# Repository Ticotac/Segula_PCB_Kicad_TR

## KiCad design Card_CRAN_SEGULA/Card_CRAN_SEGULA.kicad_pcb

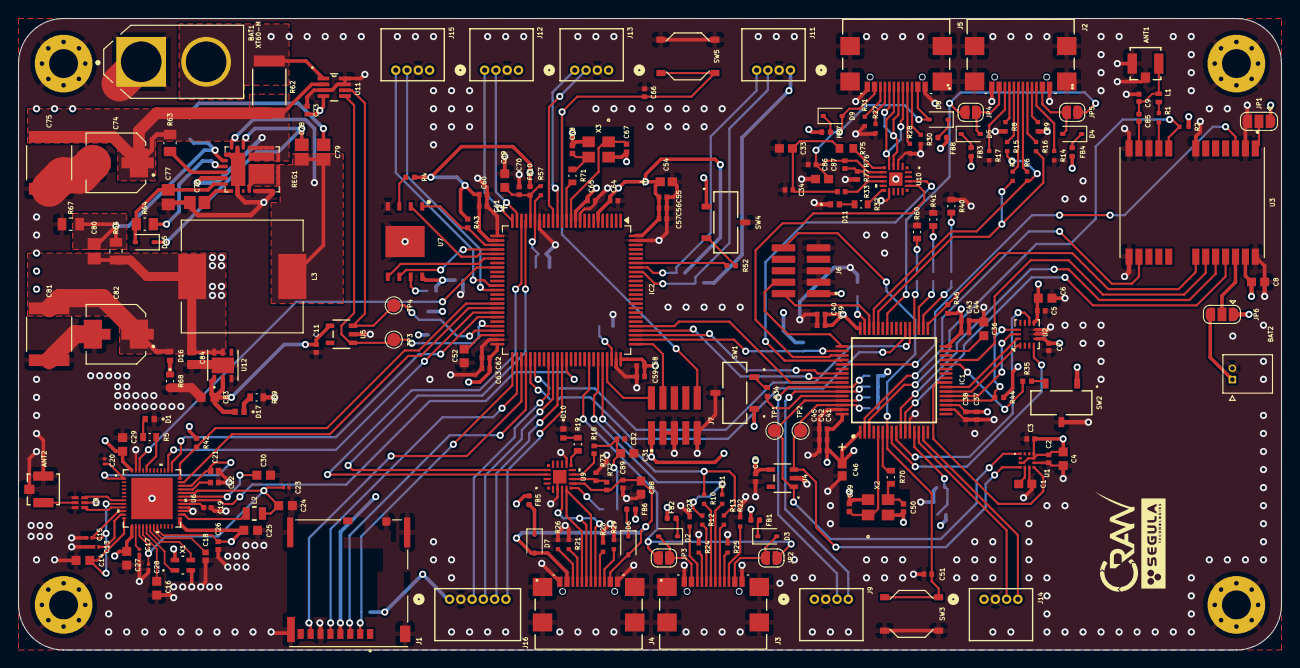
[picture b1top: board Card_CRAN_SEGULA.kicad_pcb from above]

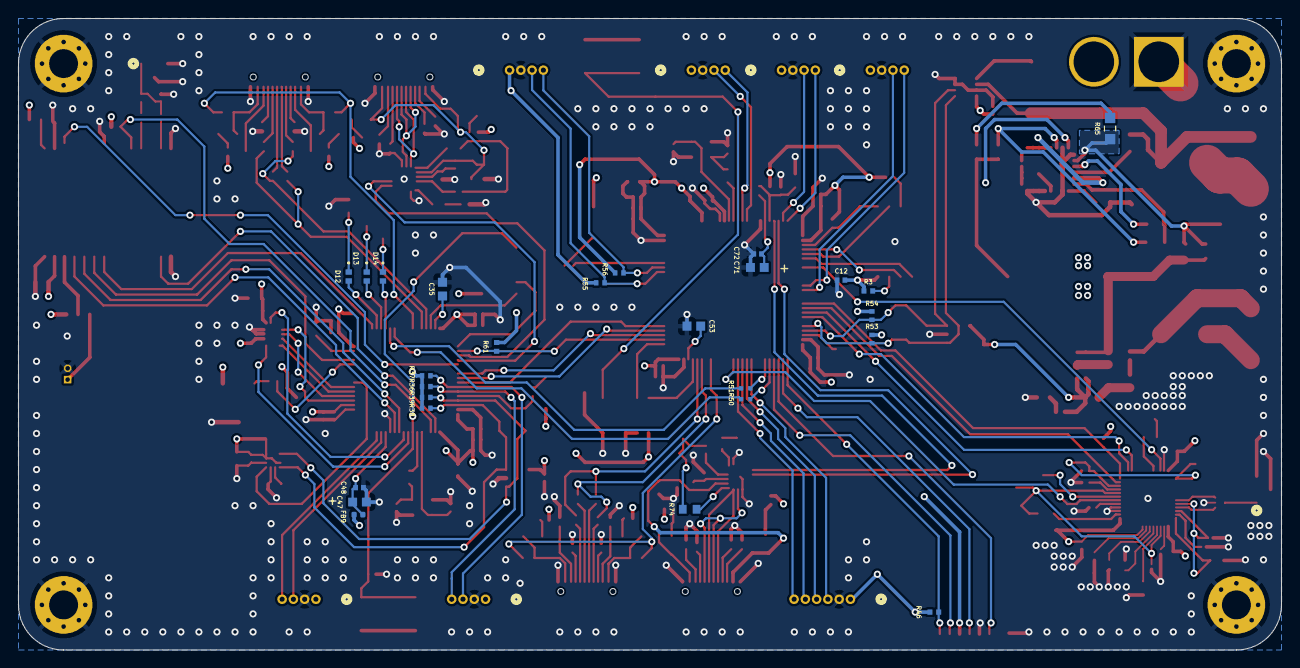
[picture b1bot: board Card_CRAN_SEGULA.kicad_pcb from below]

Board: 4 copper layers, 140.0 x 70.0 mm, 246 parts (26 on the bottom side), 193 nets.

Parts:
ANT1, ANT2: RECE.20279.001E.01; CON3_RECE.20279.001E.01_TAL
BAT1: XT60-M; AMASS_XT60-M
BAT2: 530480210; MOLEX_530480210
C1: 220nF; CAPC17595_87N_KEM
C2, C3, C10, C11, C12, C32, C34, C37, C38, C39, C40, C41, C42, C43, C44, C45, C48, C51, C55, C56, C57, C58, C59, C60, C61, C62, C63, C64, C65, C66, C70, C72, C73, C86, C89: 100nF; CAPC1005X55N
C4, C83, C84: 10uF; CAPC1608X100N
C5: 0.1uF; CAPC1005X55N
C6, C16, C29, C30, C35, C36, C52, C53: 2.2uF; CAPC1608X100N
C7, C9, C19: 10nF; CAPC1005X55N
C8, C31, C33, C87, C88: 1uF; CAPC17595_90N_KEM
C13, C23: 0.47uF; CAPC0603X33N
C14, C24, C25, C27: 4.7uF; CAPC1608X100N
C15, C20: 100nF; CAPC0603X33N
C17: 22nF; CAPC0603X33N
C18: 1uF; CAPC1005X70N
C21: 2.2uF; CAPC1005X70N
C22, C26: 1uF; CAPC1005X60N
C28: 0.22uF; CAPC0603X33N
C46, C54: 10uF; CAPMP2.1X1.25_1N_KEM
C47, C69, C71: 1uF; TACL_AVX
C49, C50, C67, C68: 10pF; CAP_0402C_AVX
C74, C82: 100uF; CAP_EEEFPV101XAV
C75, C81: 47uF; CAP_C5750X7R1V476M230KC
C76, C77: 2.2uF; CAPC220145_140N_KEM
C78, C79: 100nF; CAPC230155_120N_KEM
C80: 4.7nF; CAPC220145_100N_KEM
C85: 22pF; CAPC1005X55N
D1, D13: Blue; 599-0091-007F_DIA
D2, D3, D4, D5, D6, D7, D8, D9, D15: SD103AWS; D_SOD-323
D10, D11: RED; 599-0001-007F_DIA
D12, D14: Yellow; 599-0004-007F_DIA
D16: LED; 599-0081-007F_DIA
D17: Green; 599-0081-007F_DIA
FB1, FB2, FB3, FB4, FB5, FB6, FB7, FB8, FB9, FB10: FerriteBead_Small; L_0402_1005Metric
H1, H2, H3, H4: MountingHole_Pad; MountingHole_3.2mm_M3_Pad_Via
IC1: STM32F405RGT6; QFP50P1200X1200X160-64N
IC2: STM32H753VIT6; LQFP-100_14x14mm_P0.5mm
J1: 503398-1892; MOLEX_503398-1892
J2, J3, J4, J5: USB4110GFA; USB4110-GF-A_GCT
J6, J7: M50-3600542R; HARWIN_M50-3600542R
J9, J11, J12, J13, J14, J15: 530480410; CONN04_530480410_MOL
J16: 530480610; CONN06_530480610_MOL
JP1, JP6: SolderJumper_3_Open; SolderJumper-3_P1.3mm_Open_RoundedPad1.0x1.5mm
JP2, JP3, JP4, JP5: SolderJumper_2_Open; SolderJumper-2_P1.3mm_Open_RoundedPad1.0x1.5mm
L1: 27nH; INDC1006X60N
L2: 3.3uH; WE-PMI_0805_H1
L3: 15uH; IND_SRP1265A-150M
R1, R2, R50, R51: 10R; RES_ERA2AKD100X
R3, R4, R34, R35, R42, R43, R44, R45, R46, R52, R61: 10kR; RESC1105X40N
R5, R41: 100R; RES_ERJPA3D1000V
R6, R7, R10, R11, R12, R13, R15, R16: 22R; RES_ERA2AKD220X
R8, R14, R20, R23, R25, R26, R27, R30: 100kR; RES_ERJ2RKF1003X
R9, R17, R21, R22, R24, R28, R29, R31: 5.1kR; RES_ERJ2RKF5101X
R18, R33: 1kR; RESC1005X40N
R19, R32, R40, R60: 330R; RES_ERJPA3D3300V
R36, R37, R38, R39, R53, R54, R55, R56: 4.7kR; RESC1005X40N
R57: 47R; RES_ERA2AED470X
R62: 0.01R; RES_PE2512_YAG
R63, R64: 10kR; RESC2012X70N
R65: 19.6kR; RES_ERJ-PB6B1962V
R66: 6.8kR; RESC2012X60N
R67: 1.3kR; RK73H2ATTD1301F
R68: 560R; RES_ERJPA3F5600V
R69: 240R; RES_ERJPA3F2400V
R70, R71: 620R; RES_ERJPA3F6200V
R72, R76: 22.1kR; RESC1005X40N
R73, R77: 47.5kR; RESC1005X40N
R74, R75: 0R; RESC1508X50N
REG1: MIC26903YJL-TR; MIC24054YJLTR
SW1, SW2, SW4: TDD01H0SB1R; SOT_TDDSB1R_CNK
SW3, SW5: SMD-BUTTON_4P-5.2X5.2X1.5MM-SKQGADE010_; SW4-SMD-5.2X5.2X1.5MM
TP1, TP2, TP3, TP4: TestPoint; TestPoint_Pad_D1.5mm
U1: IIS2MDCTR
U2: IIM-42652; Bosch_LGA-14_3x2.5mm_P0.5mm
U3: NEO-M9N-00B; XCVR_NEO-M9N-00B
U4, U5: 24CW1280T-I/OT; SOT-23-5_2P9X1P6_MCH
U6: NRF7002-QFAA-R; QFN48_6X6_NOR
U7: W25N01GVZEIG_TR; SON127P800X600X80-9N-D
U8: DPX165950DT-8148A1; RF_5049A1_TDK
U9, U10: CP2102N-A02-GQFN20R; QFN20_SIL
U11: INA219AIDCNR; DCN8
U12: LD39200PU33R; SON_DFN6_3X3_STM
X1: NX2016SA-40M-STD-CZS-3; NX2016SA-40M-STD-CZS-3_NDK
X2, X3: ABM8G-25.000MHZ-4Y-T3; ABM8G_ABR

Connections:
+5V: C80.1, C81.1, C82.1, C84.1, D16.2 (A), FB1.1, FB2.2, FB3.1, FB4.2, FB5.1, FB6.2, FB7.1, FB8.2, L3.2, R66.1, U12.5 (EN), U12.6 (IN)
ADC123_0_COM: IC2.16 (PC1), J13.3
ADC123_1_COM: IC2.15 (PC0), J13.4
BOOT0_COM: IC2.94 (BOOT0), R52.1
BOOT0_NAV: IC1.60 (BOOT0), R34.1
BOOT1_NAV: IC1.28 (PB2), R35.1
FLASH_CS: IC2.28 (PA4), R43.2, U7.1 (~CS)
FLASH_MISO: IC2.30 (PA6), U7.2 (DO_(IO1))
FLASH_MOSI: IC2.31 (PA7), U7.5 (DI_(IO0))
FLASH_SCK: IC2.29 (PA5), U7.6 (CLK)
GND: ANT1.2 (GND), ANT1.3 (GND), ANT2.2 (GND), ANT2.3 (GND), BAT1.1 (-), BAT2.2, C1.2, C2.2, C3.2, C4.2, C5.2, C6.2, C7.2, C8.1, C9.1, C10.2, C11.2, C12.1, C13.1, C14.2, C15.1, C16.1, C17.2, C18.1, C19.1, C20.1, C21.1, C22.1, C23.2, C24.2, C25.2, C26.1, C27.1, C28.1, C29.2, C30.1, C31.2, C32.2, C33.2, C34.2, C35.2, C36.2, C37.2, C38.2, C39.2, C40.2, C41.2, C42.2, C43.2, C44.2, C45.2, C46.2, C47.2, C48.2, C49.2, C50.1, C51.2, C52.2, C53.2, C54.2, C55.2, C56.2, C57.2, C58.2, C59.2, C60.2, C61.2, C62.2, C63.2, C64.2, C65.2, C66.2, C67.2, C68.1, C69.2, C70.1, C71.2, C72.1, C73.1, C74.2, C75.2, C76.2, C77.2, C81.2, C82.2, C83.2, C84.2, C86.2, C87.2, C88.2, C89.2, D1.1 (K), D10.1 (K), D11.1 (K), H1.1, H2.1, H3.1, H4.1, IC1.12 (VSSA), IC1.18 (VSS_1), IC1.63 (VSS_2), IC2.10 (VSS), IC2.19 (VSSA), IC2.26 (VSS), IC2.49 (VSS), IC2.74 (VSS), IC2.99 (VSS), J1.6 (VSS), J1.9 (VSS__1), J1.P1 (SHIELD), J1.P2 (SHIELD__1), J1.P3 (SHIELD__2), J1.P4 (SHIELD__3), J2.15 (S1), J2.16 (S2), J2.17 (S3), J2.18 (S4), J2.A1/B12 (GND), J2.A12/B1 (GND), J3.15 (S1), J3.16 (S2), J3.17 (S3), J3.18 (S4), J3.A1/B12 (GND), J3.A12/B1 (GND), J4.15 (S1), J4.16 (S2), J4.17 (S3), J4.18 (S4), J4.A1/B12 (GND), J4.A12/B1 (GND), J5.15 (S1), J5.16 (S2), J5.17 (S3), J5.18 (S4), J5.A1/B12 (GND), J5.A12/B1 (GND), J6.3, J6.5, J6.9, J7.3, J7.5, J7.9, J9.2, J11.2, J12.2, J13.2, J14.2, J15.2, J16.2, JP1.3 (B), R8.1, R9.1, R14.2, R17.1, R20.1, R21.1, R22.1, R23.2, R24.1, R25.1, R26.2, R27.1, R28.1, R29.1, R30.2, R31.1, R40.2, R41.1, R60.2, R67.2, R68.2, R69.2, R73.2, R77.2, REG1.2 (PGND), REG1.5 (PGND), REG1.6 (PGND), REG1.7 (PGND), REG1.8 (PGND), REG1.21 (PGND), REG1.23 (SGND), REG1.31 (PGND), SW1.2, SW2.2, SW3.3 (B0), SW3.4 (B1), SW4.2, SW5.3 (B0), SW5.4 (B1), U1.6 (GND_1), U1.8 (GND_2), U2.6 (GND), U2.7 (GND), U3.2 (D_SEL), U3.7 (V_USB), U3.10 (GND), U3.12 (GND__1), U3.13 (GND__2), U3.24 (GND__3), U4.2 (VSS), U5.2 (VSS), U6.27 (BUCKVSS), U6.28 (BUCKVSS), U6.47 (VSS), U6.49 (VSS), U7.4 (GND), U7.9 (EP), U8.2, U8.4, U8.6, U9.3 (GND), U9.12 (GND__1), U9.21 (GND__2), U10.3 (GND), U10.12 (GND__1), U10.21 (GND__2), U11.3 (GND), U11.7 (A0), U11.8 (A1), U12.3 (GND), U12.7 (GND), X1.2, X1.4, X2.2, X2.4, X3.2, X3.4
GNSS_BAT_BACKUP: JP6.2 (C), U3.22 (V_BCKP)
GNSS_CLK: IC1.29 (PB10), U3.19 (SCL/SPI_CLK)
GNSS_CS: IC1.33 (PB12), R45.1, U3.18 (SDA/SPI_CS_N)
GNSS_LNA_EN: IC1.2 (PC13), U3.14 (LNA_EN)
GNSS_NRST: IC1.3 (PC14), R2.2, U3.8 (RESET_N)
GNSS_PPS: IC1.53 (PC12), U3.3 (TIMEPULSE)
GNSS_SDI: IC1.11 (PC3), U3.21 (RXD/SPI_MOSI)
GNSS_SDO: IC1.10 (PC2), U3.20 (TXD/SPI_MISO)
HSE_IN_COM: C67.1, IC2.12 (PH0), X3.1
HSE_IN_NAV: C49.1, IC1.5 (PH0), X2.1
HSE_OUT_COM: IC2.13 (PH1), R71.2
HSE_OUT_NAV: IC1.6 (PH1), R70.2
I2C2_SDA_COM: IC2.93 (PB7), J11.4, R56.2
I2C2_SDA_NAV: IC1.59 (PB7), J9.4, R36.2
I2C2_SLC_COM: IC2.92 (PB6), J11.3, R55.2
I2C2_SLC_NAV: IC1.58 (PB6), J9.3, R37.2
I2C_SCL_COM: IC2.46 (PB10), R53.2, TP3.1, U5.1 (SCL), U11.5 (SCL)
I2C_SCL_NAV: IC1.61 (PB8), R39.2, TP1.1, U1.1 (SCL/SPC), U4.1 (SCL)
I2C_SDA_COM: IC2.47 (PB11), R54.2, TP4.1, U5.3 (SDA), U11.6 (SDA)
I2C_SDA_NAV: IC1.62 (PB9), R38.2, TP2.1, U1.4 (SDA/SDI/SDO), U4.3 (SDA)
IMU_ACC_INT: IC1.8 (PC0), U2.4 (INT1/INT)
IMU_CS: IC1.20 (PA4), R44.2, U2.12 (AP_CS)
IMU_GYR_INT: IC1.9 (PC1), U2.9 (INT2/FSYNC/CLKIN)
IMU_SCLK: IC1.21 (PA5), U2.13 (AP_SCL/AP_SCLK)
IMU_SD0: IC1.22 (PA6), U2.1 (AP_SDO/AP_AD0)
IMU_SDI: IC1.23 (PA7), U2.14 (AP_SDA/AP_SDIO/AP_SDI)
LED_A_NAV: D12.2 (A), IC1.34 (PB13)
LED_B_NAV: D13.2 (A), IC1.35 (PB14)
LED_C_NAV: D14.2 (A), IC1.36 (PB15)
MAG_INT: IC1.24 (PC4), U1.7 (INT/DRDY)
NRST_COM: C66.1, IC2.14 (NRST), J7.10, SW5.1 (A0), SW5.2 (A1)
NRST_NAV: C51.1, IC1.7 (NRST), J6.10, SW3.1 (A0), SW3.2 (A1)
unnamed: ANT1.1 (SIGNAL), C9.2, C85.1, L1.1
unnamed: ANT2.1 (SIGNAL), U8.5
unnamed: C31.1, C32.1, R18.2, R74.2
unnamed: C33.1, C34.1, R33.2, R75.2
unnamed: C50.2, R70.1, X2.3
unnamed: C52.1, IC2.48 (VCAP)
unnamed: C53.1, IC2.73 (VCAP)
unnamed: C68.2, R71.1, X3.3
unnamed: C79.2, R65.1
unnamed: D1.2 (A), R5.2
unnamed: D2.2 (A), J3.A4/B9 (VBUS), JP3.1 (A)
unnamed: D2.1 (K), FB2.1
unnamed: D3.2 (A), J3.A9/B4 (VBUS), JP2.1 (A)
unnamed: D3.1 (K), FB1.2
unnamed: D4.2 (A), J2.A4/B9 (VBUS), JP5.1 (A)
unnamed: D4.1 (K), FB4.1
unnamed: D5.2 (A), J2.A9/B4 (VBUS), JP4.1 (A)
unnamed: D5.1 (K), FB3.2
unnamed: D6.1 (K), FB6.1
unnamed: D7.1 (K), FB5.2
unnamed: D8.1 (K), FB8.1
unnamed: D9.1 (K), FB7.2
unnamed: D10.2 (A), R19.1
unnamed: D11.2 (A), R32.1
unnamed: D12.1 (K), R40.1
unnamed: D13.1 (K), R41.2
unnamed: D14.1 (K), R60.1
unnamed: C77.1, D15.2 (A), R64.1, REG1.28 (VDD)
unnamed: D16.1 (K), R68.1
unnamed: D17.1 (K), R69.1
unnamed: C36.1, IC1.31 (VCAP_1)
unnamed: C35.1, IC1.47 (VCAP_2)
unnamed: J2.A5 (CC1), R9.2
unnamed: J2.B5 (CC2), R17.2
unnamed: J2.A7 (DN1), R7.2
unnamed: J2.B7 (DN2), R16.2
unnamed: J2.A6 (DP1), R6.2
unnamed: J2.B6 (DP2), R15.1
unnamed: J2.A8 (SBU1), R8.2
unnamed: J2.B8 (SBU2), R14.1
unnamed: J3.A5 (CC1), R24.2
unnamed: J3.B5 (CC2), R22.2
unnamed: J3.A7 (DN1), R11.2
unnamed: J3.B7 (DN2), R12.2
unnamed: J3.A6 (DP1), R10.2
unnamed: J3.B6 (DP2), R13.1
unnamed: J3.A8 (SBU1), R25.2
unnamed: J3.B8 (SBU2), R23.1
unnamed: J4.A5 (CC1), R21.2
unnamed: J4.B5 (CC2), R29.2
unnamed: J4.A8 (SBU1), R20.2
unnamed: J4.B8 (SBU2), R26.1
unnamed: J5.A5 (CC1), R28.2
unnamed: J5.B5 (CC2), R31.2
unnamed: J5.A8 (SBU1), R27.2
unnamed: J5.B8 (SBU2), R30.1
unnamed: JP1.2 (C), U3.1 (SAFEBOOT_N)
unnamed: BAT2.1, JP6.3 (B)
unnamed: L1.2, R1.1
unnamed: R34.2, SW1.3
unnamed: R35.2, SW2.3
unnamed: R52.2, SW4.3
unnamed: C76.1, REG1.1 (PVDD)
unnamed: C1.1, U1.5 (C1)
unnamed: C85.2, U3.11 (RF_IN)
unnamed: R1.2, U3.9 (VCC_RF)
unnamed: L2.1, U6.26 (BUCKOUT)
unnamed: C14.1, C15.2, U6.8 (PAVDD<1>), U6.10 (PAVDD<0>), U6.12 (PALDO)
unnamed: R5.1, U6.44 (SW_CTRL0)
unnamed: R3.2, U7.7 (~HOLD_(IO3))
unnamed: R4.2, U7.3 (~WP_(IO2))
unnamed: R72.2, R73.1, U9.8 (VBUS)
unnamed: R74.1, U9.6 (VDD)
unnamed: R18.1, U9.9 (~RST)
unnamed: R19.2, U9.11 (~SUSPEND)
unnamed: R76.2, R77.1, U10.8 (VBUS)
unnamed: R75.1, U10.6 (VDD)
unnamed: R33.1, U10.9 (~RST)
unnamed: R32.2, U10.11 (~SUSPEND)
REG_BST: C78.2, D15.1 (K), REG1.20 (BST)
REG_CS: C78.1, C79.1, L3.1, REG1.4 (SW), REG1.9 (SW), REG1.10 (SW), REG1.11 (SW), REG1.12 (SW), REG1.22 (CS), REG1.29 (EPAD)
REG_EN: R63.2, REG1.26 (EN)
REG_FB: C80.2, R65.2, R66.2, R67.1, REG1.24 (FB)
REG_PG: R64.2, REG1.25 (PG)
REG_VIN: C74.1, C75.1, R62.2, R63.1, REG1.13 (PVIN), REG1.14 (PVIN), REG1.15 (PVIN), REG1.16 (PVIN), REG1.17 (PVIN), REG1.18 (PVIN), REG1.19 (PVIN), REG1.27 (VIN), REG1.30 (PVIN), U11.2 (VIN-)
SD_CLK: IC2.52 (PB13), J1.5 (CLK)
SD_CS: IC2.51 (PB12), J1.2 (CD/DAT3^2), R46.2
SD_MISO: IC2.53 (PB14), J1.7 (DAT0)
SD_MOSI: IC2.54 (PB15), J1.3 (CMD)
SPI3_CS_COM: IC1.50 (PA15), IC2.77 (PA15), R61.2
SPI3_MISO_COM: IC1.56 (PB4), IC2.79 (PC11)
SPI3_MOSI_COM: IC1.57 (PB5), IC2.80 (PC12)
SPI3_SCK_COM: IC1.55 (PB3), IC2.78 (PC10)
SWCLK_COM: IC2.76 (PA14), J7.4
SWCLK_NAV: IC1.49 (PA14), J6.4
SWDIO_COM: IC2.72 (PA13), J7.2
SWDIO_NAV: IC1.46 (PA13), J6.2
TIM4_CH1_COM: IC2.59 (PD12), J16.3
TIM4_CH2_COM: IC2.60 (PD13), J16.4
TIM4_CH3_COM: IC2.61 (PD14), J16.5
TIM4_CH4_COM: IC2.62 (PD15), J16.6
UART1_RX_COM: IC2.23 (PA1), U9.18 (TXD)
UART1_RX_NAV: IC1.52 (PC11), U10.18 (TXD)
UART1_TX_COM: IC2.22 (PA0), U9.17 (RXD)
UART1_TX_NAV: IC1.51 (PC10), U10.17 (RXD)
UART2_RX_COM: IC2.25 (PA3), J12.4
UART2_RX_NAV: IC1.15 (PA1), J14.4
UART2_TX_COM: IC2.24 (PA2), J12.3
UART2_TX_NAV: IC1.14 (PA0_WKUP), J14.3
UART3_RX_COM: IC2.56 (PD9), R51.2
UART3_RX_NAV: IC1.38 (PC7), R50.1
UART3_TX_COM: IC2.55 (PD8), R50.2
UART3_TX_NAV: IC1.37 (PC6), R51.1
UART4_RX_COM: IC2.37 (PE7), J15.4
UART4_TX_COM: IC2.38 (PE8), J15.3
UART_DN_COM: J4.A7 (DN1), J4.B7 (DN2), U9.5 (D-)
UART_DN_NAV: J5.A7 (DN1), J5.B7 (DN2), U10.5 (D-)
UART_DP_COM: J4.A6 (DP1), J4.B6 (DP2), U9.4 (D+)
UART_DP_NAV: J5.A6 (DP1), J5.B6 (DP2), U10.4 (D+)
UART_VBUS_COM: C88.1, C89.1, D6.2 (A), D7.2 (A), J4.A4/B9 (VBUS), J4.A9/B4 (VBUS), R72.1, U9.7 (VREGIN)
UART_VBUS_NAV: C86.1, C87.1, D8.2 (A), D9.2 (A), J5.A4/B9 (VBUS), J5.A9/B4 (VBUS), R76.1, U10.7 (VREGIN)
USB_DN_COM: IC2.70 (PA11), R11.1, R12.1
USB_DN_NAV: IC1.44 (PA11), R7.1, R16.1
USB_DP_COM: IC2.71 (PA12), R10.1, R13.2
USB_DP_NAV: IC1.45 (PA12), R6.1, R15.2
USB_VBUS_COM: IC2.68 (PA9), JP2.2 (B), JP3.2 (B)
USB_VBUS_NAV: IC1.42 (PA9), JP4.2 (B), JP5.2 (B)
VDDA_COM: C69.1, C70.2, FB10.1, IC2.21 (VDDA), R57.1
VDDA_NAV: C47.1, C48.1, FB9.2, IC1.13 (VDDA)
VIN+: BAT1.2 (+), R62.1, U11.1 (VIN+)
VREF+_COM: C71.1, C72.2, IC2.20 (VREF+), R57.2
WIFI_2.4GH: U6.9 (TXRF<0>), U8.1
WIFI_5GH: U6.7 (TXRF<1>), U8.3
WIFI_AFELDO: C18.2, U6.19 (AFELDO)
WIFI_BUCKEN: IC2.63 (PC6), U6.30 (BUCKEN)
WIFI_BUCKVMID: C19.2, U6.29 (BUCKVMID)
WIFI_BUCVBATS: C2.1, C3.1, C4.1, C5.1, C6.1, C7.1, C8.2, C10.1, C11.1, C12.2, C25.1, C26.2, C27.2, C29.1, C30.2, C37.1, C38.1, C39.1, C40.1, C41.1, C42.1, C43.1, C44.1, C45.1, C46.1, C54.1, C55.1, C56.1, C57.1, C58.1, C59.1, C60.1, C61.1, C62.1, C63.1, C64.1, C65.1, C73.2, C83.1, D17.2 (A), FB9.1, FB10.2, IC1.1 (VBAT), IC1.19 (VDD_1), IC1.32 (VDD_2), IC1.48 (VDD_3), IC1.64 (VDD_4), IC2.6 (VBAT), IC2.11 (VDD), IC2.27 (VDD), IC2.50 (VDD), IC2.75 (VDD), IC2.100 (VDD), J1.4 (VDD), J6.1, J7.1, J9.1, J11.1, J12.1, J13.1, J14.1, J15.1, J16.1, JP1.1 (A), JP6.1 (A), R2.1, R3.1, R4.1, R36.1, R37.1, R38.1, R39.1, R42.1, R43.1, R44.1, R45.2, R46.1, R53.1, R54.1, R55.1, R56.1, R61.1, SW1.1, SW2.1, SW4.1, U1.3 (CS), U1.9 (VDD), U1.10 (VDD_IO), U2.5 (VDDIO), U2.8 (VDD), U3.23 (VCC), U4.4 (VCC), U5.4 (VCC), U6.13 (VBAT), U6.20 (AFEVBAT), U6.25 (BUCKVBAT), U6.31 (BUCVBATS), U6.48 (IOVDD), U7.8 (VCC), U11.4 (VS), U12.1 (OUT), U12.2 (ADJ/SENSE)
WIFI_CLK: IC2.42 (PE12), U6.35 (QSPI_CLK)
WIFI_CS: IC2.41 (PE11), R42.2, U6.36 (QSPI_SS)
WIFI_DIGVDD: C22.2, U6.33 (DIGVDD)
WIFI_INT: IC2.33 (PC5), U6.46 (HOST_IRQ)
WIFI_MISO: IC2.43 (PE13), U6.38 (QSPI_DATA1)
WIFI_MOSI: IC2.44 (PE14), U6.37 (QSPI_DATA0)
WIFI_PWRIOVDD: C20.2, C21.2, U6.1 (OTPVDD), U6.34 (PWRIOVDD)
WIFI_RFBUCKVDD: C23.1, C24.1, C28.2, L2.2, U6.15 (RFBUCKVDD), U6.32 (PWRBUCKVDD)
WIFI_RFVDD: C17.1, U6.14 (RFVDD)
WIFI_SXLDO: C13.2, U6.11 (SXLDO)
WIFI_XOLDO: C16.2, U6.16 (XOLDO)
WIFI_XON: U6.18 (XON), X1.3
WIFI_XOP: U6.17 (XOP), X1.1

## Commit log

2025-04-30 Premier commit
2025-05-01 Message de validation
2025-06-03 Carte presque fini avant la dernière vérification
2025-07-07 MàJ 07/07/2025
